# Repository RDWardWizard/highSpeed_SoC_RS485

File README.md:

# highSpeed_SoC_RS485
The high speed bike has smart battery with RS485 communication. We put a PCB with the following components:
  >RS485 to TTL converter
  >ESP32 board
  >Resistors for LED-bar

The PCB is connected with 8-core cable. The 8 wires are soldered on the LED bar.
We will show 0, 1, 2, 3, 4, 5-6, 7-8, 9-10 bars.

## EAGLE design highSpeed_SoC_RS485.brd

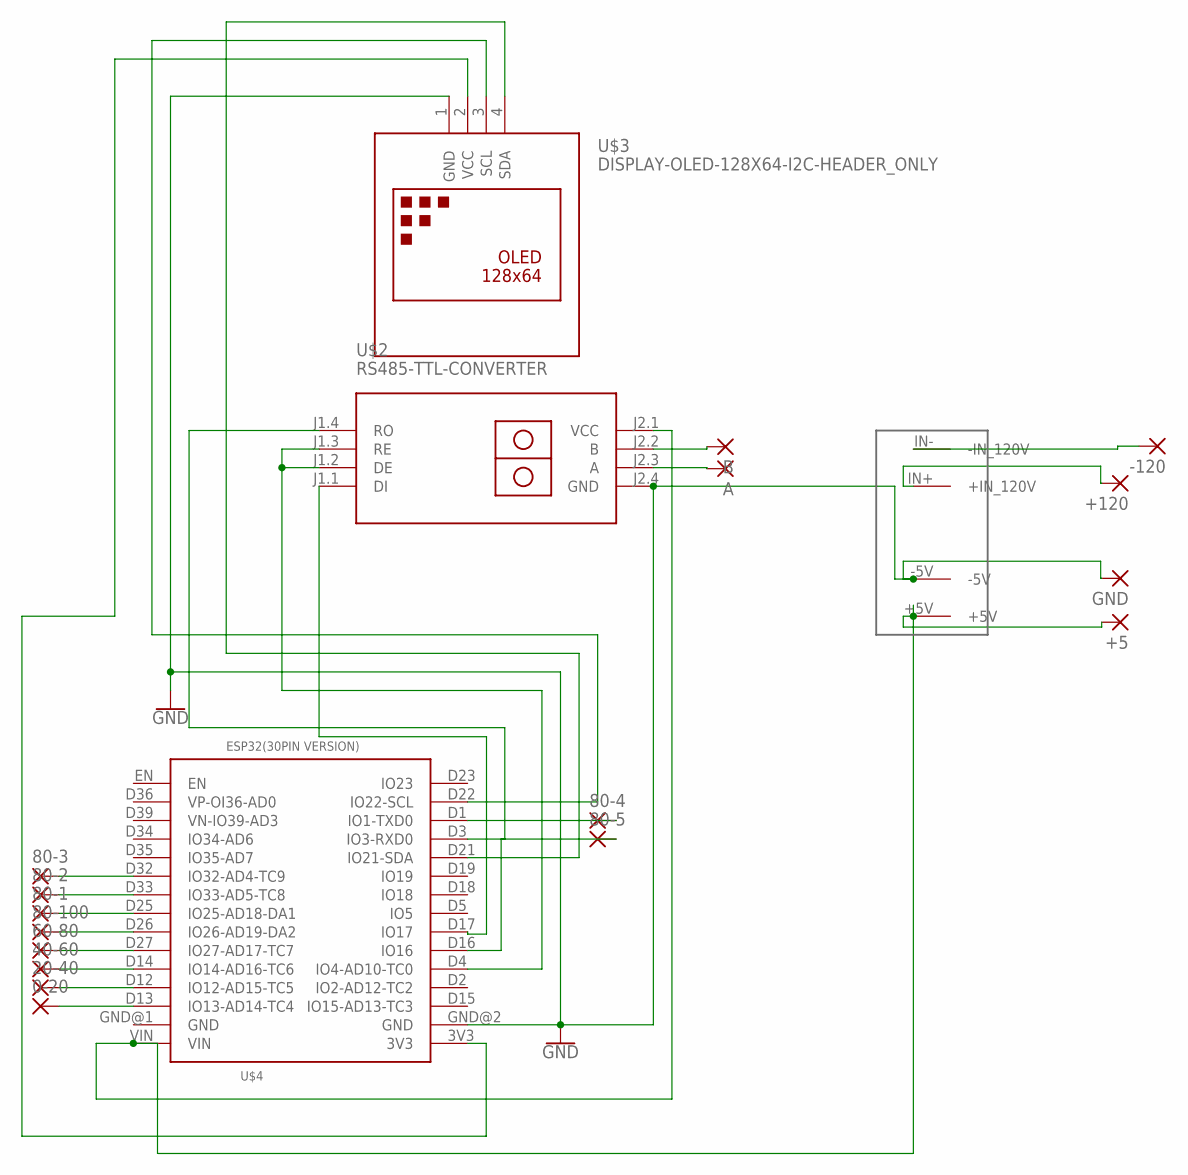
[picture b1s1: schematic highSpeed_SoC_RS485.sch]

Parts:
0-20, 20-40, 40-60, 60-80, 80-1, 80-2, 80-3, 80-4, 80-5, 80-100: 2,54/1,0
+5, +120: 2,54/1,0
-120: 2,54/1,0
A: 2,54/1,0
B: 2,54/1,0
GND: 2,54/1,0
U$1: DC-DC_CONVERTER_WOLF1
U$2: RS485-TTL-CONVERTER
U$3: DISPLAY-OLED-128X64-I2C-HEADER_ONLY
U$4: ESP32(30PIN_VERSION)

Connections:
GND: GND.1, U$1.-5V, U$2.J2.4 (GND), U$3.1 (GND), U$4.GND@2 (GND)
unnamed: U$3.4 (SDA), U$4.D21 (IO21-SDA)
unnamed: 0-20.1, U$4.D13 (IO13-AD14-TC4)
unnamed: +5.1, U$1.+5V, U$2.J2.1 (VCC), U$4.VIN
unnamed: U$2.J1.4 (RO), U$4.D16 (IO16)
unnamed: B.1, U$2.J2.2 (B)
unnamed: U$2.J1.1 (DI), U$4.D17 (IO17)
unnamed: +120.1, U$1.IN+ (+IN_120V)
unnamed: U$3.2 (VCC), U$4.3V3
unnamed: U$3.3 (SCL), U$4.D22 (IO22-SCL)
unnamed: A.1, U$2.J2.3 (A)
unnamed: -120.1, U$1.IN- (-IN_120V)
unnamed: 20-40.1, U$4.D12 (IO12-AD15-TC5)
unnamed: U$2.J1.2 (DE), U$2.J1.3 (RE), U$4.D4 (IO4-AD10-TC0)
unnamed: 40-60.1, U$4.D14 (IO14-AD16-TC6)
unnamed: 60-80.1, U$4.D27 (IO27-AD17-TC7)
unnamed: 80-100.1, U$4.D26 (IO26-AD19-DA2)
unnamed: 80-1.1, U$4.D25 (IO25-AD18-DA1)
unnamed: 80-2.1, U$4.D33 (IO33-AD5-TC8)
unnamed: 80-3.1, U$4.D32 (IO32-AD4-TC9)
unnamed: 80-4.1, U$4.D1 (IO1-TXD0)
unnamed: 80-5.1, U$4.D3 (IO3-RXD0)

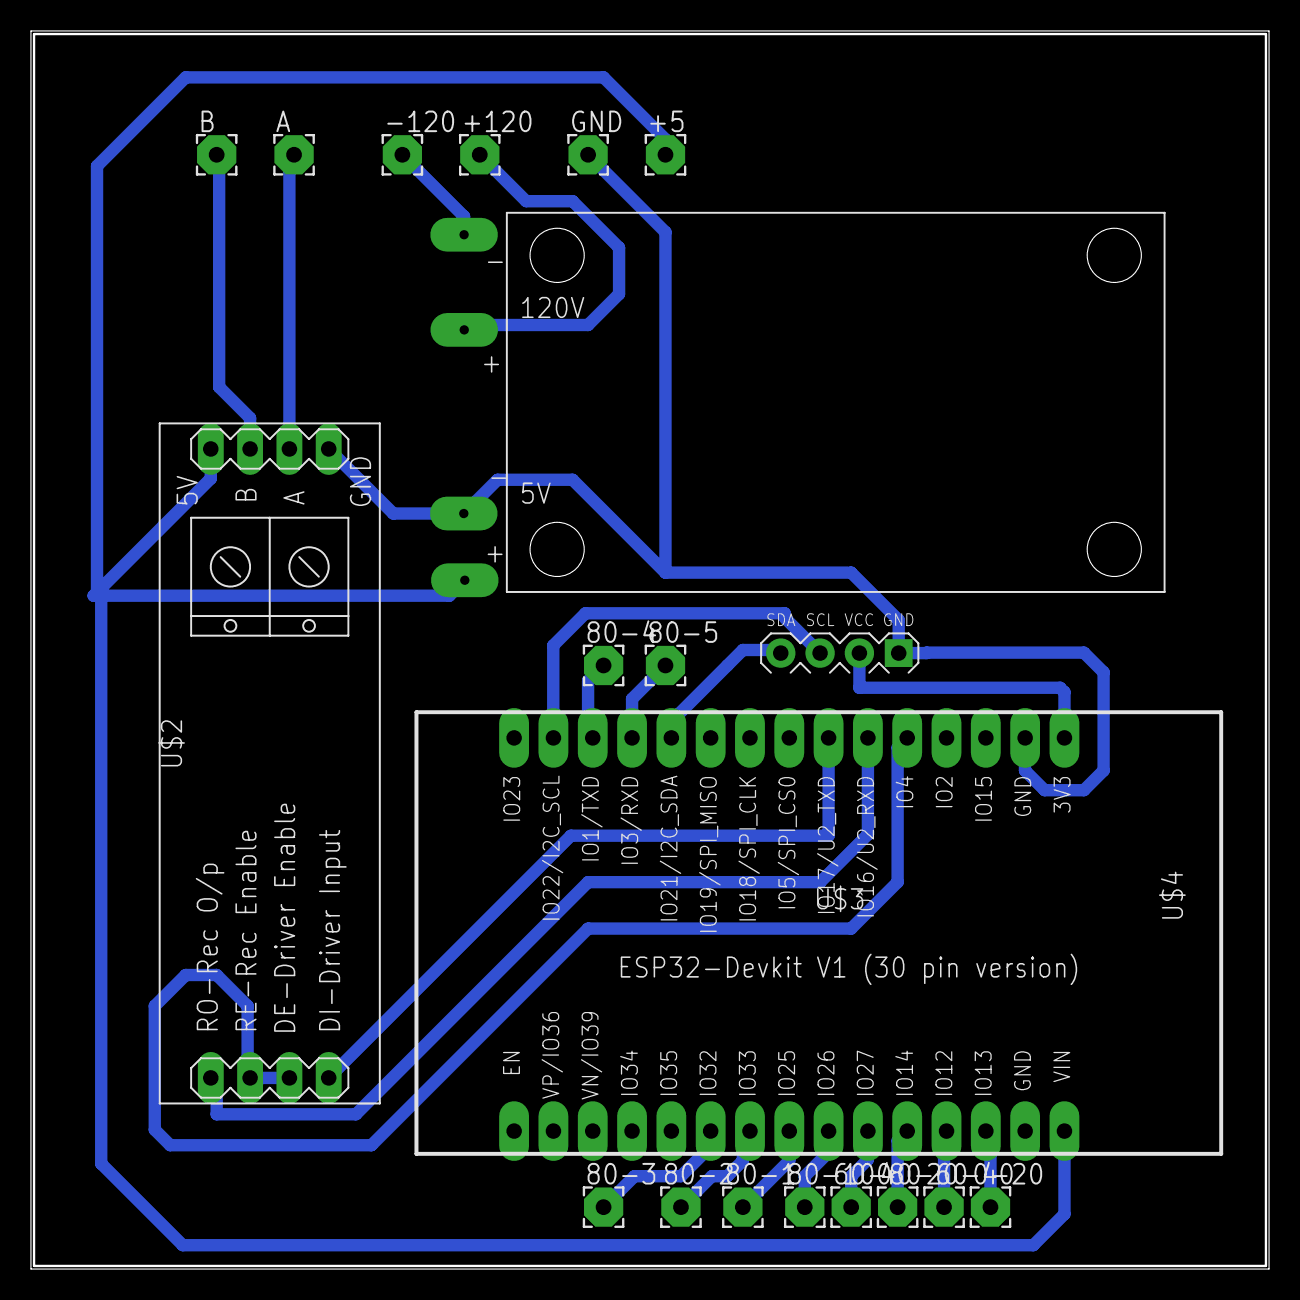
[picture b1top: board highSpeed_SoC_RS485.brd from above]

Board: 2 copper layers, 79.8 x 79.8 mm, 20 parts (0 on the bottom side), 22 nets.

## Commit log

2021-10-08 Described the PCB.
2021-10-08 Added the EAGLE files with PDF

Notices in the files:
parts and their libraries:
SparkFun-PowerSymbols: Licensing: Creative Commons ShareAlike 4.0 International - https://creativecommons.org/licenses/by-sa/4.0
